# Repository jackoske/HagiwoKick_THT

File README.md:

# HagiwoKick

# Notes / Design Issues

- Q: Provide 5v from Arduino or directly from Eurorack 5V rail. A: We chose the former
- Patch submodule uses 22uF ceramic instead of 10uF electrolytic

# ToDo

Place capacitors closer to the Arduino, if that's what we want to supress noise on

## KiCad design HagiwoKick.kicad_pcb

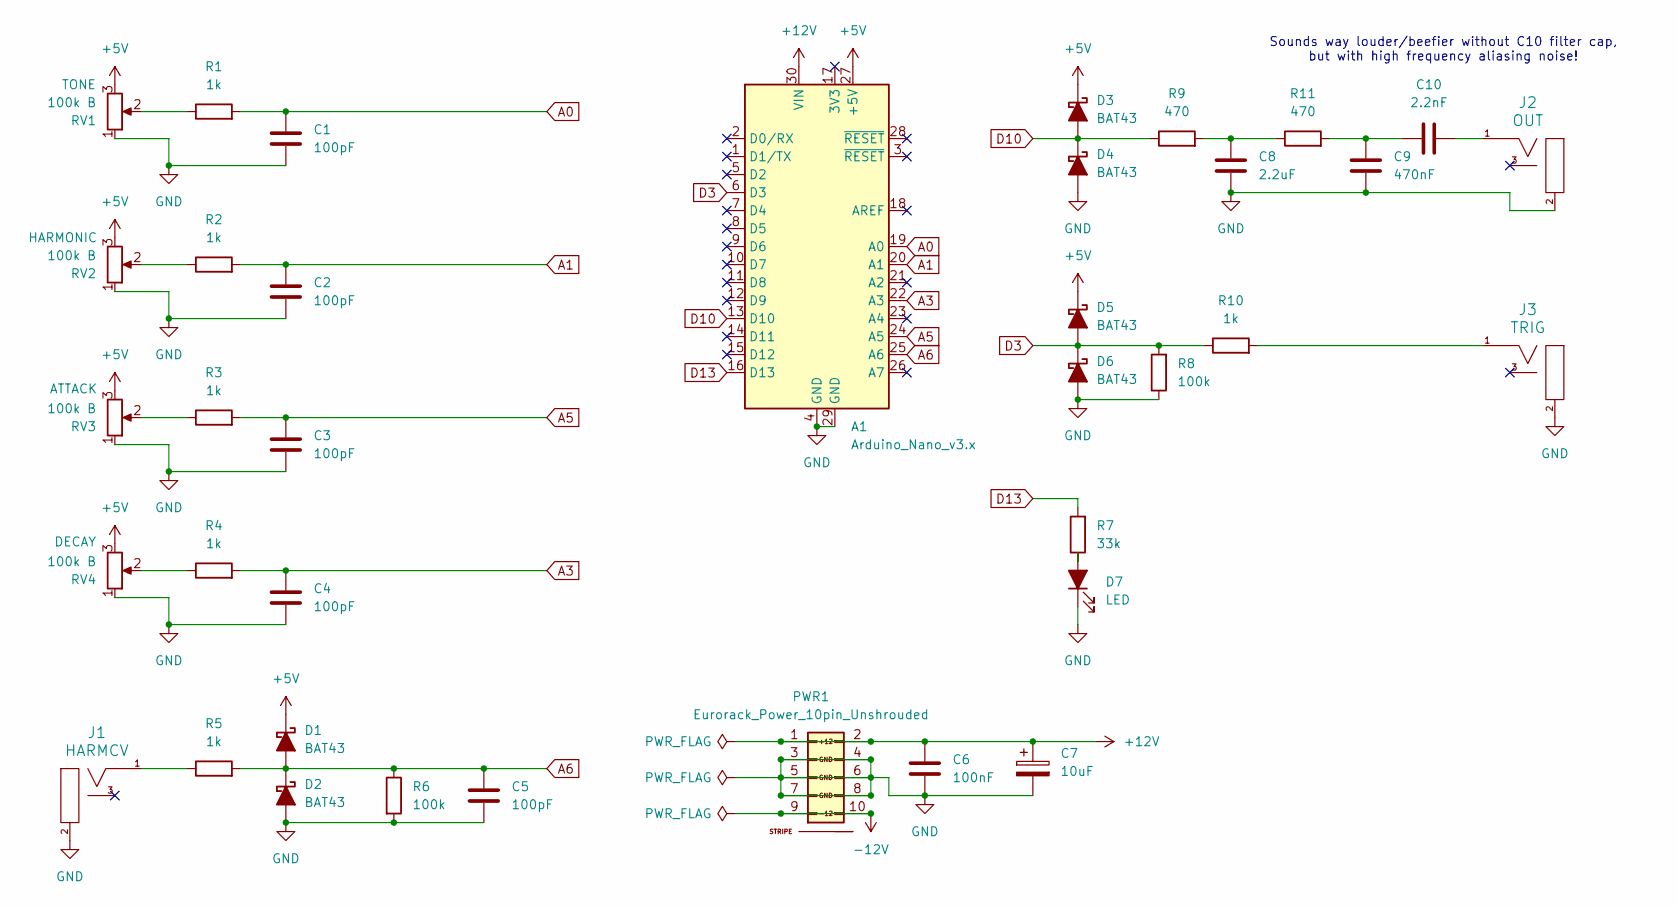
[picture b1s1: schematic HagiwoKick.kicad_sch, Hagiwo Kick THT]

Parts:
A1: Arduino_Nano_v3.x; Arduino_Nano
C1, C2, C3, C4, C5: 100pF; C_Disc_D3.8mm_W2.6mm_P2.50mm
C6: 100nF; C_Disc_D3.8mm_W2.6mm_P2.50mm
C7: 10uF; CP_Radial_D4.0mm_P2.00mm
C8: 2.2uF; C_Disc_D3.8mm_W2.6mm_P2.50mm
C9: 470nF; C_Disc_D3.8mm_W2.6mm_P2.50mm
C10: 2.2nF; C_Disc_D3.8mm_W2.6mm_P2.50mm
D1, D2, D3, D4, D5, D6: BAT43; D_DO-35_SOD27_P7.62mm_Horizontal_Widened_No_K
D7: LED; LED_D5.0mm
J1: HARMCV; EighthInch_PJ398SM_3mmNPTH; Part Number WQP-WQP518MA
J2: OUT; EighthInch_PJ398SM_3mmNPTH; Part Number WQP-WQP518MA
J3: TRIG; EighthInch_PJ398SM_3mmNPTH; Part Number WQP-WQP518MA
PWR1: Eurorack_Power_10pin_Unshrouded; IDC-Header_2x05_P2.54mm_Vertical_Euro_Power_Striped_Thicker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; Part Number 1-1002FBV0T
R1, R2, R3, R4, R5, R10: 1k; R_Axial_DIN0207_L6.3mm_D2.5mm_P7.62mm_Horizontal
R6, R8: 100k; R_Axial_DIN0207_L6.3mm_D2.5mm_P7.62mm_Horizontal
R7: 33k; R_Axial_DIN0207_L6.3mm_D2.5mm_P7.62mm_Horizontal
R9, R11: 470; R_Axial_DIN0207_L6.3mm_D2.5mm_P7.62mm_Horizontal
RV1, RV2, RV3, RV4: 100k B; Pot_9mm_DShaft_RemovedPins4_5

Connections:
+5V: A1.27 (+5V), D1.1 (K), D3.1 (K), D5.1 (K), RV1.3, RV2.3, RV3.3, RV4.3
+12V: A1.30 (VIN), C6.1, C7.1, PWR1.1 (+12V), PWR1.2 (+12V)
-12V: PWR1.9 (-12V), PWR1.10 (-12V)
A0: A1.19 (A0), C1.1, R1.2
A1: A1.20 (A1), C2.1, R2.2
A3: A1.22 (A3), C4.1, R4.2
A5: A1.24 (A5), C3.1, R3.2
A6: A1.25 (A6), C5.1, D1.2 (A), D2.1 (K), R5.2, R6.1
D3: A1.6 (D3), D5.2 (A), D6.1 (K), R8.2, R10.1
D10: A1.13 (D10), D3.2 (A), D4.1 (K), R9.1
D13: A1.16 (D13), R7.2
GND: A1.4 (GND), A1.29 (GND), C1.2, C2.2, C3.2, C4.2, C5.2, C6.2, C7.2, C8.2, C9.2, D2.2 (A), D4.2 (A), D6.2 (A), D7.1 (K), J1.2 (SHEILD), J2.2 (SHEILD), J3.2 (SHEILD), PWR1.3 (GND), PWR1.4 (GND), PWR1.5 (GND), PWR1.6 (GND), PWR1.7 (GND), PWR1.8 (GND), R6.2, R8.1, RV1.1, RV2.1, RV3.1, RV4.1
unnamed: C8.1, R9.2, R11.1
unnamed: C9.1, C10.1, R11.2
unnamed: D7.2 (A), R7.1
unnamed: J1.1 (SIG), R5.1
unnamed: C10.2, J2.1 (SIG)
unnamed: J3.1 (SIG), R10.2
unnamed: R1.1, RV1.2
unnamed: R2.1, RV2.2
unnamed: R3.1, RV3.2
unnamed: R4.1, RV4.2

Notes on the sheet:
Sounds way louder/beefier without C10 filter cap, but with high frequency aliasing noise!

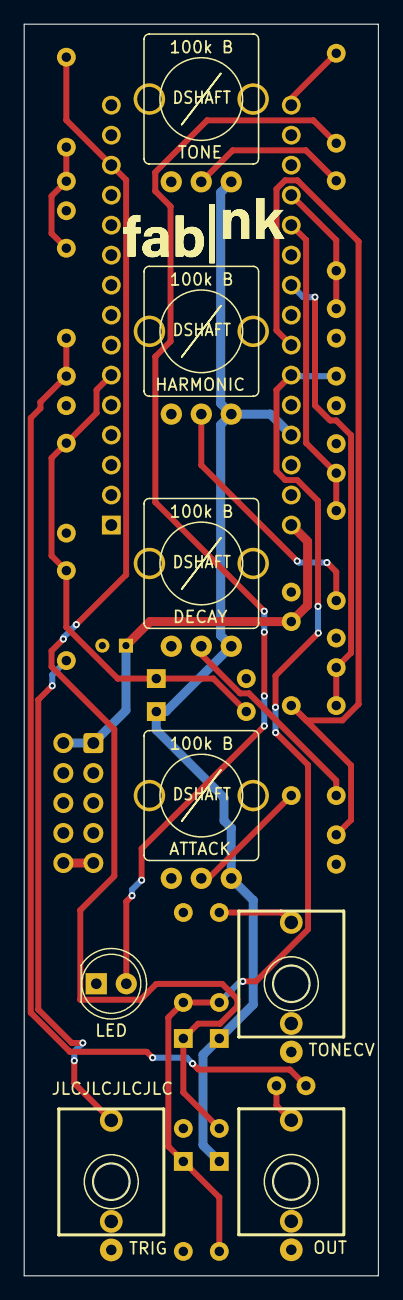
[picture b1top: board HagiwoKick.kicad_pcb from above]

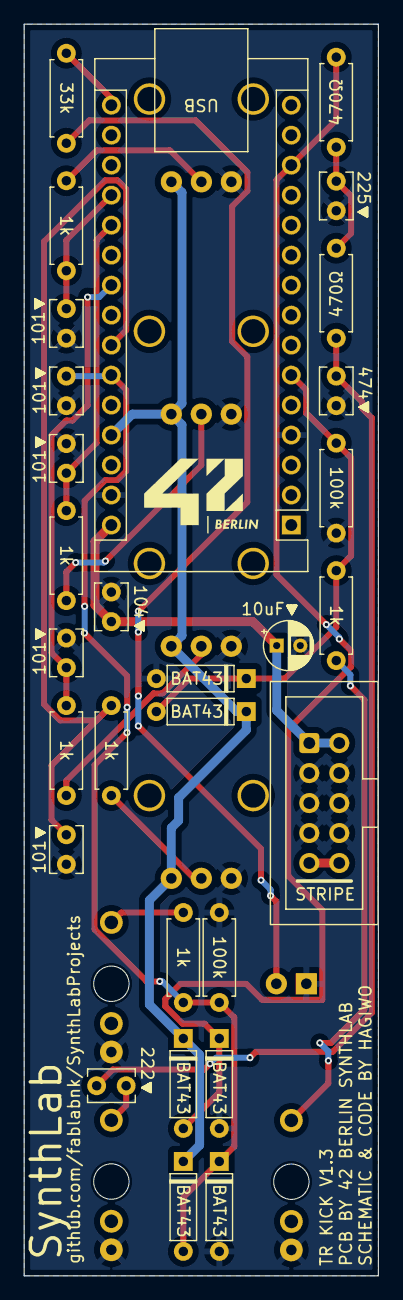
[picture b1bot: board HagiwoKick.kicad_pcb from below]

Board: 2 copper layers, 30.0 x 106.0 mm, 37 parts (29 on the bottom side), 22 nets.

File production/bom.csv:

Designator,Footprint,Quantity,Value,LCSC Part #
A1,Arduino_Nano,1,Arduino_Nano_v3.x,
"C1, C2, C3, C4, C5",C_Disc_D3.8mm_W2.6mm_P2.50mm,5,100pF,
C10,C_Disc_D3.8mm_W2.6mm_P2.50mm,1,2.2nF,
C6,C_Disc_D3.8mm_W2.6mm_P2.50mm,1,100nF,
C7,CP_Radial_D4.0mm_P2.00mm,1,10uF,
C8,C_Disc_D3.8mm_W2.6mm_P2.50mm,1,2.2uF,
C9,C_Disc_D3.8mm_W2.6mm_P2.50mm,1,470nF,
"D1, D2, D3, D4, D5, D6",D_DO-35_SOD27_P7.62mm_Horizontal_Widened_No_K,6,BAT43,
D7,LED_D5.0mm,1,LED,
J1,EighthInch_PJ398SM_3mmNPTH,1,TUNECV,
J2,EighthInch_PJ398SM_3mmNPTH,1,OUT,
J3,EighthInch_PJ398SM_3mmNPTH,1,TRIG,
PWR1,IDC-Header_2x05_P2.54mm_Vertical_Euro_Power_Striped_ThickerText,1,Eurorack_Power_10pin_Unshrouded,
"R1, R10, R2, R3, R4, R5",R_Axial_DIN0207_L6.3mm_D2.5mm_P7.62mm_Horizontal,6,1k,
"R11, R9",R_Axial_DIN0207_L6.3mm_D2.5mm_P7.62mm_Horizontal,2,470,
"R6, R8",R_Axial_DIN0207_L6.3mm_D2.5mm_P7.62mm_Horizontal,2,100k,
R7,R_Axial_DIN0207_L6.3mm_D2.5mm_P7.62mm_Horizontal,1,33k,
"RV1, RV2, RV3, RV4",Pot_9mm_DShaft_RemovedPins4_5,4,100k B,

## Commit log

2024-08-13 latest updates
2024-09-15 Added BuildNotes.md. Removed production folder
2024-09-22 v1.1 ready for final check
2024-12-01 updating after Dmitri's changes
2024-12-14 added code to repo
2024-12-14 switched positions of TRIG and OUT outputs
2024-12-14 reversed orientated of pots on schematic to make +5V rightmost pin and updated routing. This completes v1.2
2024-12-15 added v1.2 production files
2025-01-11 minor repositioning - V1.2 ready for fabrication
2025-02-12 adding second lasercut ready template wth black and readme
2025-02-25 corrected silkscreening issue that TUNE should be TONE and other minor fixed for v1.3
2025-02-26 flipped knob_tone in code to account for the pot wiring in our circuit
